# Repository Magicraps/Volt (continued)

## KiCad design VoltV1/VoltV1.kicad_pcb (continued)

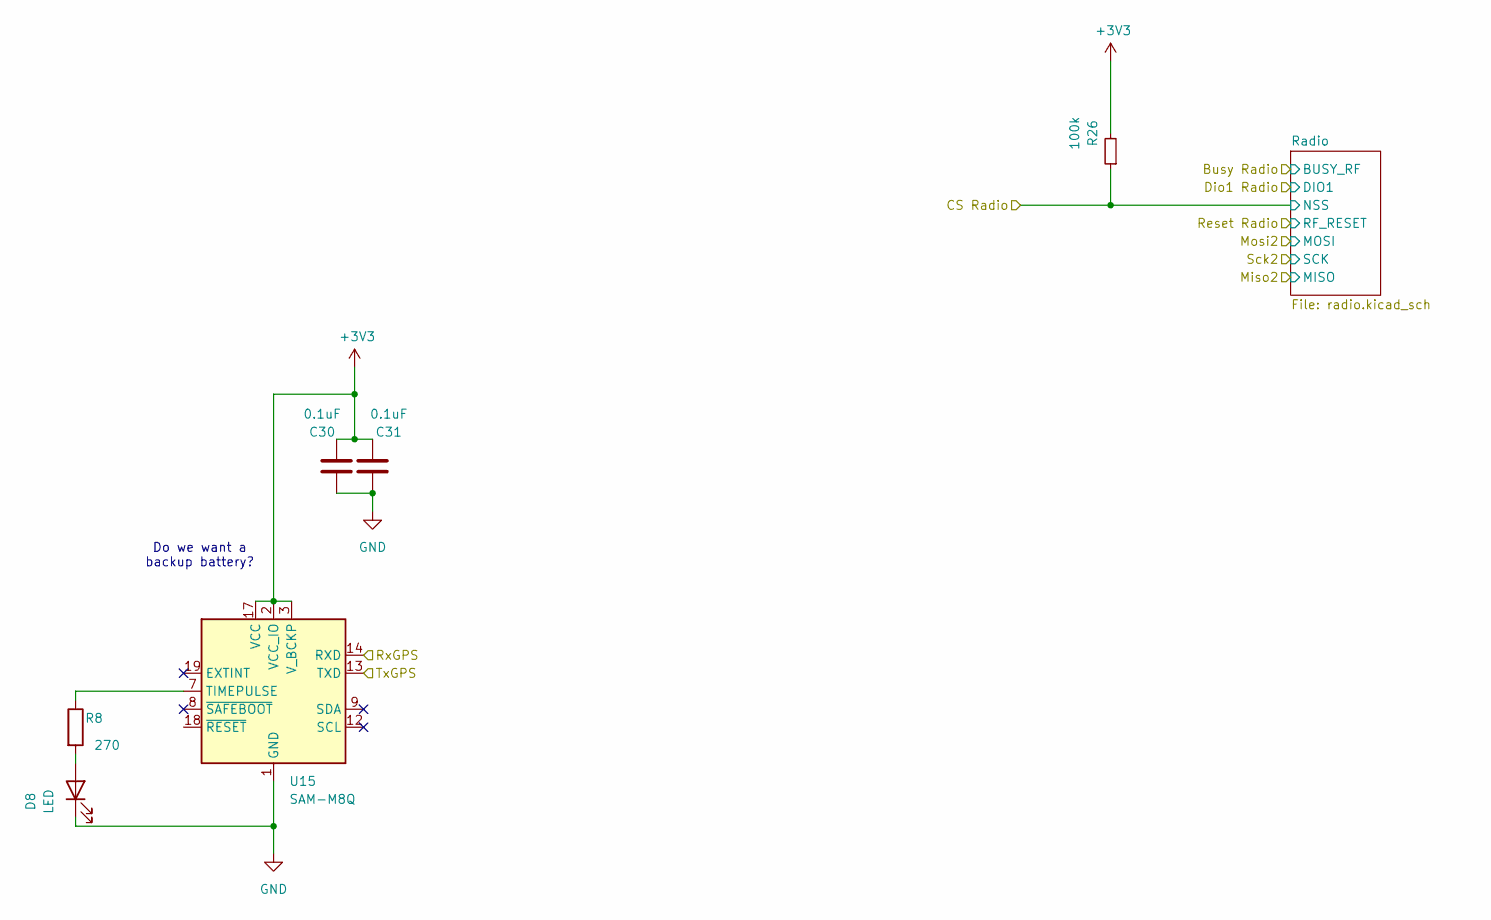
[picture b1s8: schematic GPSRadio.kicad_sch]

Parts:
C30, C31: 0.1uF; C_0402_1005Metric
D8: LED; LED_0603_1608Metric
R8: 270; R_0402_1005Metric
R26: 100k; R_0402_1005Metric; LCSC C25077
U15: SAM-M8Q; ublox_SAM-M8Q

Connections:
+3V3: C30.2, C31.2, R26.2, U15.2 (VCC_IO), U15.3 (V_BCKP), U15.17 (VCC); also elsewhere on the board
/GPSRadio/CS Radio: R26.1; also elsewhere on the board
/GPSRadio/RxGPS: U15.14 (RXD); also elsewhere on the board
/GPSRadio/TxGPS: U15.13 (TXD); also elsewhere on the board
GND: C30.1, C31.1, D8.1 (K), U15.1 (GND), U15.4 (GND), U15.5 (GND), U15.6 (GND), U15.10 (GND), U15.11 (GND), U15.15 (GND), U15.16 (GND), U15.20 (GND); also elsewhere on the board
unnamed: D8.2 (A), R8.2
unnamed: R8.1, U15.7 (TIMEPULSE)

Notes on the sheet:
Do we want a backup battery?

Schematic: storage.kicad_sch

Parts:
C21, C22: .1uF; C_0402_1005Metric
C23: 10uF; C_0402_1005Metric
R4: 100k; R_0402_1005Metric
R6, R7: 10k; R_0402_1005Metric
R31: 100k; R_0402_1005Metric; LCSC C25077
U2: S25FL512SAGMF
U6: MB85RS64; SOIC127P600X155-8_R159_68_374R15

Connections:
+3.3V: C21.1, C22.2, C23.1, R4.1, R6.1, R7.1, R31.2, U2.2 (VCC), U2.14 (VIO/RFU), U6.8 (VCC); also elsewhere on the board
/GPSRadio/Miso2: U2.8 (SO/IO1), U6.2 (MISO); also elsewhere on the board
/GPSRadio/Mosi2: U2.15 (SI/IO0), U6.5 (MOSI); also elsewhere on the board
/GPSRadio/Sck2: U2.16 (SCK), U6.6 (SCK); also elsewhere on the board
/mcu/FRAM CS: R31.1, U6.1 (~CS); also elsewhere on the board
/mcu/Flash CS: R4.2, U2.7 (CS#); also elsewhere on the board
/mcu/Hold Flash: U2.1 (HOLD#/IO3); also elsewhere on the board
GND: C21.2, C22.1, C23.2, U2.10 (VSS), U6.4 (GND); also elsewhere on the board
unnamed: R7.2, U6.7 (~HOLD)
unnamed: R6.2, U6.3 (~WP)

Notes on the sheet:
Internal pullup on WP and Reset
Flash Datasheet
MB85RS64PNF-G-JNE1

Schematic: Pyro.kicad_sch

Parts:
C33, C34: 1nF; C_0402_1005Metric
C35: 10uF; C_0402_1005Metric
C37: .1uF; C_0402_1005Metric
Q1: STL66DN3LLH5; POWERFLAT5X6_STL66_STM
R9, R10, R11, R12: R; R_0402_1005Metric
U20: SOIC-8_3.9x4.9mm_P1.27mm

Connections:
/Pyros/Pyro0/Armed Pyro: C35.1, C37.1, U20.6 (VCC); also elsewhere on the board
/Pyros/Pyro0/Pyro0 Neg: Q1.5 (D), Q1.6 (D), R11.1
/Pyros/Pyro0/Pyro1 Neg: Q1.7 (D), Q1.8 (D), R9.1
/Pyros/PyroPWM0: U20.2 (INA); also elsewhere on the board
/Pyros/PyroPWM1: U20.4 (INB); also elsewhere on the board
/Pyros/PyroSense0: R11.2, R12.1; also elsewhere on the board
/Pyros/PyroSense1: R9.2, R10.1; also elsewhere on the board
GND: C33.1, C34.1, C35.2, C37.2, Q1.1 (S), Q1.3 (S), R10.2, R12.2, U20.3 (GND); also elsewhere on the board
unnamed: C33.2, Q1.4 (G), U20.7 (OUTA)
unnamed: C34.2, Q1.2 (G), U20.5 (OUTB)

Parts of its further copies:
C39, C40, C45, C46: 1nF; C_0402_1005Metric
C41, C47: 10uF; C_0402_1005Metric
C43, C49: .1uF; C_0402_1005Metric
Q2, Q3: STL66DN3LLH5; POWERFLAT5X6_STL66_STM
R13, R14, R15, R16, R17, R19, R20, R21: R; R_0402_1005Metric
U21, U22: SOIC-8_3.9x4.9mm_P1.27mm

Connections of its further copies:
/Pyros/Pyro0/Armed Pyro: C41.1, C43.1, C47.1, C49.1, U21.6 (VCC), U22.6 (VCC); also elsewhere on the board
/Pyros/Pyro1/Pyro0 Neg: Q2.5 (D), Q2.6 (D), R15.1
/Pyros/Pyro1/Pyro1 Neg: Q2.7 (D), Q2.8 (D), R13.1
/Pyros/Pyro2/Pyro0 Neg: Q3.5 (D), Q3.6 (D), R20.1
/Pyros/Pyro2/Pyro1 Neg: Q3.7 (D), Q3.8 (D), R17.1
/Pyros/PyroPWM2: U21.2 (INA); also elsewhere on the board
/Pyros/PyroPWM3: U21.4 (INB); also elsewhere on the board
/Pyros/PyroPWM4: U22.2 (INA); also elsewhere on the board
/Pyros/PyroPWM5: U22.4 (INB); also elsewhere on the board
/Pyros/PyroSense2: R15.2, R16.1; also elsewhere on the board
/Pyros/PyroSense3: R13.2, R14.1; also elsewhere on the board
/Pyros/PyroSense4: R20.2, R21.1; also elsewhere on the board
/Pyros/PyroSense5: R17.2, R19.1; also elsewhere on the board
GND: C39.1, C40.1, C41.2, C43.2, C45.1, C46.1, C47.2, C49.2, Q2.1 (S), Q2.3 (S), Q3.1 (S), Q3.3 (S), R14.2, R16.2, R19.2, R21.2, U21.3 (GND), U22.3 (GND); also elsewhere on the board
unnamed: C39.2, Q2.4 (G), U21.7 (OUTA)
unnamed: C40.2, Q2.2 (G), U21.5 (OUTB)
unnamed: C45.2, Q3.4 (G), U22.7 (OUTA)
unnamed: C46.2, Q3.2 (G), U22.5 (OUTB)

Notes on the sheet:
3.3V = (26V * R2)/(R1 + R2) 0.127 = R2 / (R1 + R2) -> 0.1 = R2 / (R1 + R2) R2 = 10k R1 = 90k (R2 + R1) = 100k V = IR 26V / 100k = 0.26mA Disarmed w/continuity = (3.3-0.7) * 0.1 = 0.26V Armed w/continuity = 26 * 0.1 = 2.6V

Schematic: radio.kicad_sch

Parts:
C27: 10p; C_0402_1005Metric
C28, C29, C64, C65: 100n; C_0402_1005Metric
C32, C66: 47n; C_0402_1005Metric
C67: 1u; C_0402_1005Metric
C68, C69, C72: 47p; C_0402_1005Metric
C70, C71: 1n; C_0402_1005Metric
FL1: 0900FM15K0039; Balun_Johanson_0900FM15K0039
J9: Conn_Coaxial; SMA_Molex_73251-1153_EdgeMount_Horizontal
L3: 47n; L_0603_1608Metric
R36: 10k; R_0402_1005Metric
R39, R40: 220R; R_0402_1005Metric
R41: 100R; R_0402_1005Metric
U3: SX1262IMLTRT; QFN-24-1EP_4x4mm_P0.5mm_EP2.6x2.6mm
U9: 4259-63; SC-70-6_PSM-L
Y2: ECSTXO20CSMV320EYTR; OSC_ECSTXO20CSMV320EYTR; PARTREV N/A

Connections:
+3.3V: C28.1, C29.1, C65.1, R36.1, R41.1, U3.1 (VDD_IN), U3.10 (VBAT), U3.11 (VBAT_IO), Y2.4 (VDD); also elsewhere on the board
/GPSRadio/Busy Radio: U3.14 (BUSY); also elsewhere on the board
/GPSRadio/CS Radio: U3.19 (NSS); also elsewhere on the board
/GPSRadio/Dio1 Radio: U3.13 (DIO1); also elsewhere on the board
/GPSRadio/Miso2: U3.16 (MISO); also elsewhere on the board
/GPSRadio/Mosi2: U3.17 (MOSI); also elsewhere on the board
/GPSRadio/Radio/CTRL: C70.2, R40.2, U9.4 (CTRL)
/GPSRadio/Radio/DIO2: R40.1, U3.12 (DIO2)
/GPSRadio/Radio/RF1: C68.1, U9.1 (RF1)
/GPSRadio/Radio/RF2: C69.1, U9.3 (RF2)
/GPSRadio/Radio/RFI_N: FL1.3 (RFI_N), U3.22 (RFI_N)
/GPSRadio/Radio/RFI_P: FL1.4 (RFI_P), U3.21 (RFI_P)
/GPSRadio/Radio/RFNET: C72.2, U9.5 (RFC)
/GPSRadio/Radio/RFO: FL1.1 (RFO), L3.2, U3.23 (RFO)
/GPSRadio/Radio/SW_RFI: C69.2, FL1.6 (SW_RFI)
/GPSRadio/Radio/SW_RFO: C68.2, FL1.8 (SW_RFO)
/GPSRadio/Radio/VREG: C64.1, C67.1, U3.7 (VREG)
/GPSRadio/Radio/VR_PA: C32.2, C66.2, L3.1, U3.24 (VR_PA)
/GPSRadio/Radio/XTA: R39.2, U3.3 (XTA)
/GPSRadio/Reset Radio: R36.2, U3.15 (~RESET); also elsewhere on the board
/GPSRadio/Sck2: U3.18 (SCK); also elsewhere on the board
GND: C28.2, C29.2, C32.1, C64.2, C65.2, C66.1, C67.2, C70.1, C71.1, FL1.2 (GND), FL1.5 (GND), FL1.7 (GND), FL1.9 (GND), FL1.10 (GND), J9.2 (Ext), U3.2 (GND), U3.5 (GND), U3.8 (GND), U3.20 (GND), U3.25 (GND), U9.2 (GND), Y2.1 (GROUND), Y2.2 (GROUND__1); also elsewhere on the board
unnamed: C27.1, R39.1
unnamed: C72.1, J9.1 (In)
unnamed: C71.2, R41.2, U9.6 (VDD)
unnamed: C27.2, Y2.3 (OUTPUT)

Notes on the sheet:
Coupling
0402 C0G 47 pF
Option D: SX1262 with LDO Regulator VBAT=3.3 V min. to reach +22 dBm
DIO2 Conneted t the control of the RF switch Note: DIO2 can be configured to drive an RF switch through the use of the command
Note:When entering SLEEP mode, the BUSY line is asserted high and stays high for the complete duration of the SLEEP period
The BUSY line shows if the radio is ready for a new command. BUSY low: Radio is idle and ready to accept commands. BUSY high: Radio is processing a command.
VR_PA: Values are not from my personal design and are from a different design by Kai L2:SDWL1608C47NJSTFM01
TCXO
TCXO (Temperature Compensated Crystal Oscillator) is used due to temperature variation to achieve better frequency accuracy.
Impedance-Matched Filter
RF RESET
RF Switch
Radio Design by Itamar Dekel

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
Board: 4 copper layers, 156 parts (0 on the bottom side), 141 nets, no tracks yet.

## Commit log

2025-12-16 syncing. Power not done yet
2026-03-07 merging. power stuff incomplete
2026-06-28 updates to schematic
2026-06-28 schematic updates
